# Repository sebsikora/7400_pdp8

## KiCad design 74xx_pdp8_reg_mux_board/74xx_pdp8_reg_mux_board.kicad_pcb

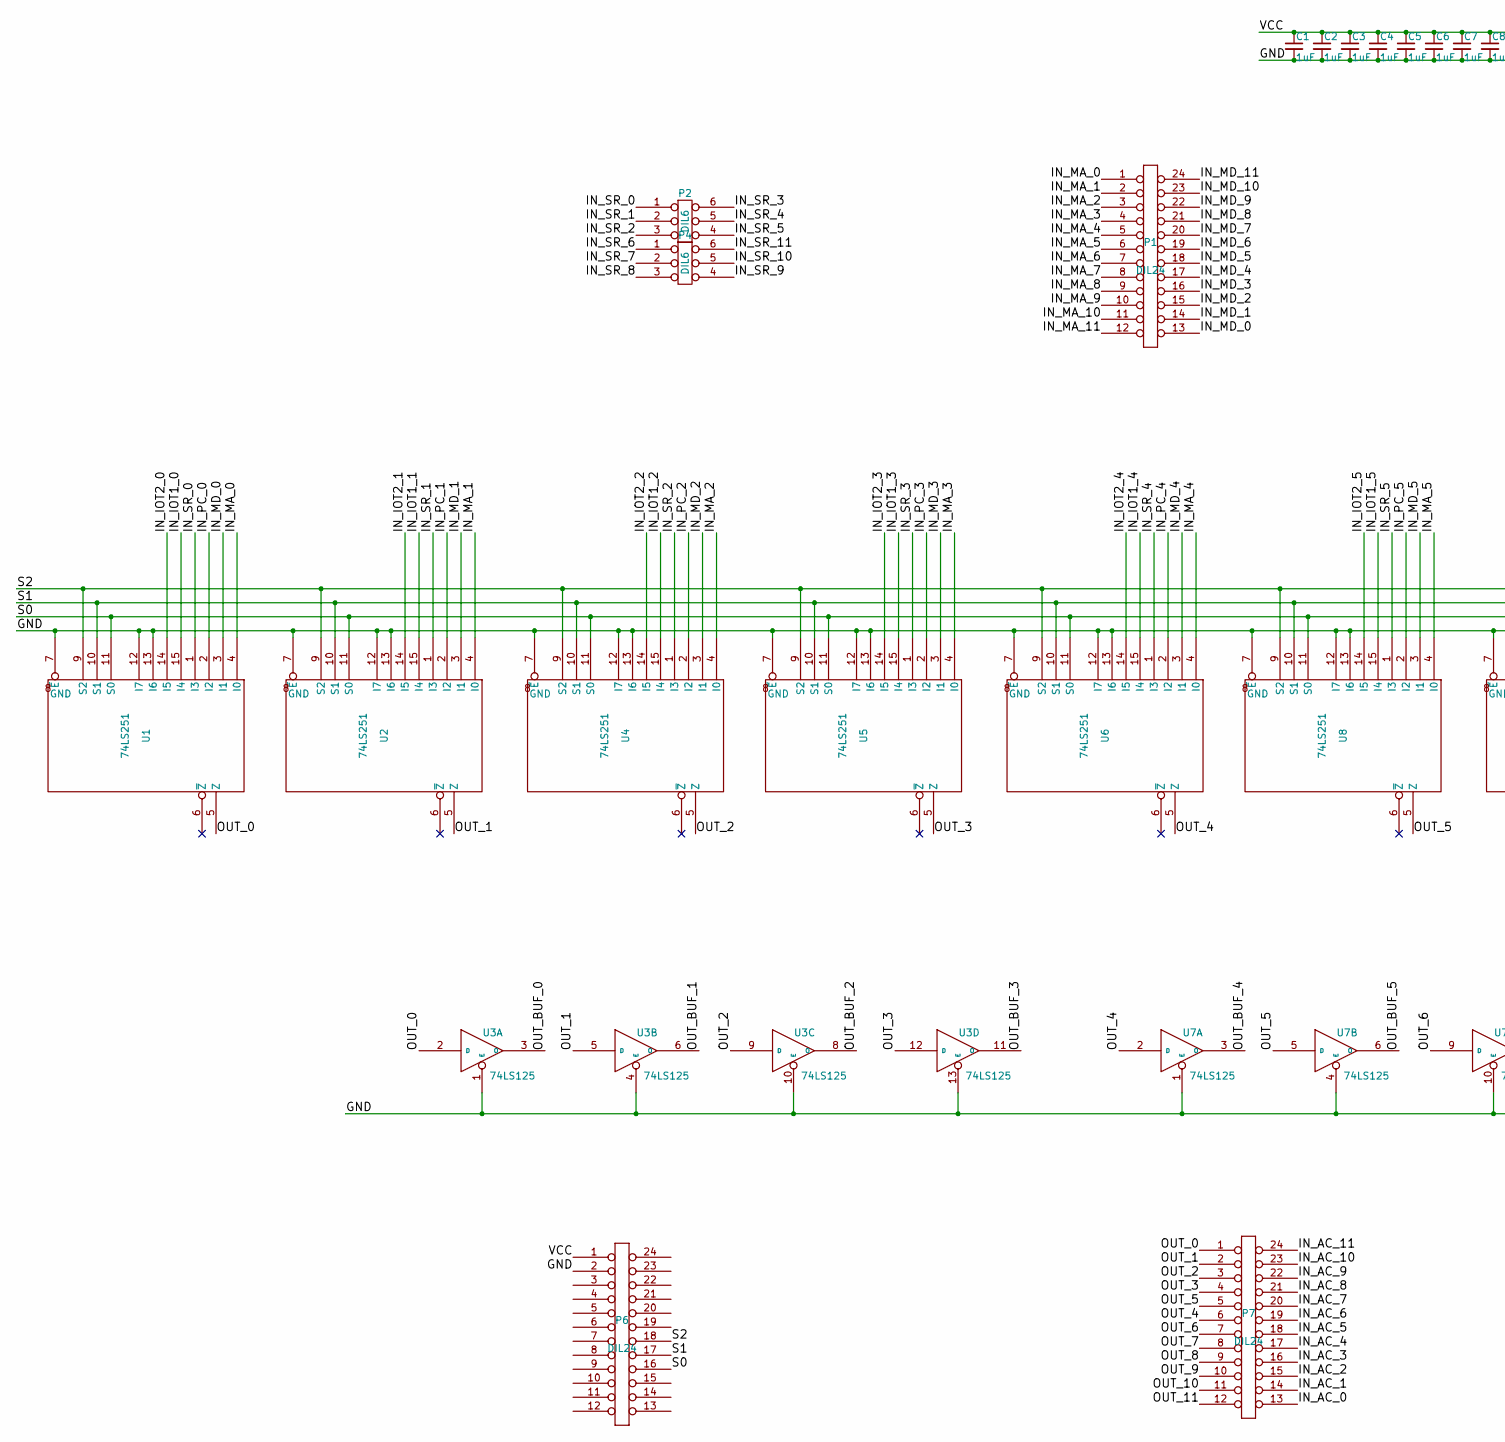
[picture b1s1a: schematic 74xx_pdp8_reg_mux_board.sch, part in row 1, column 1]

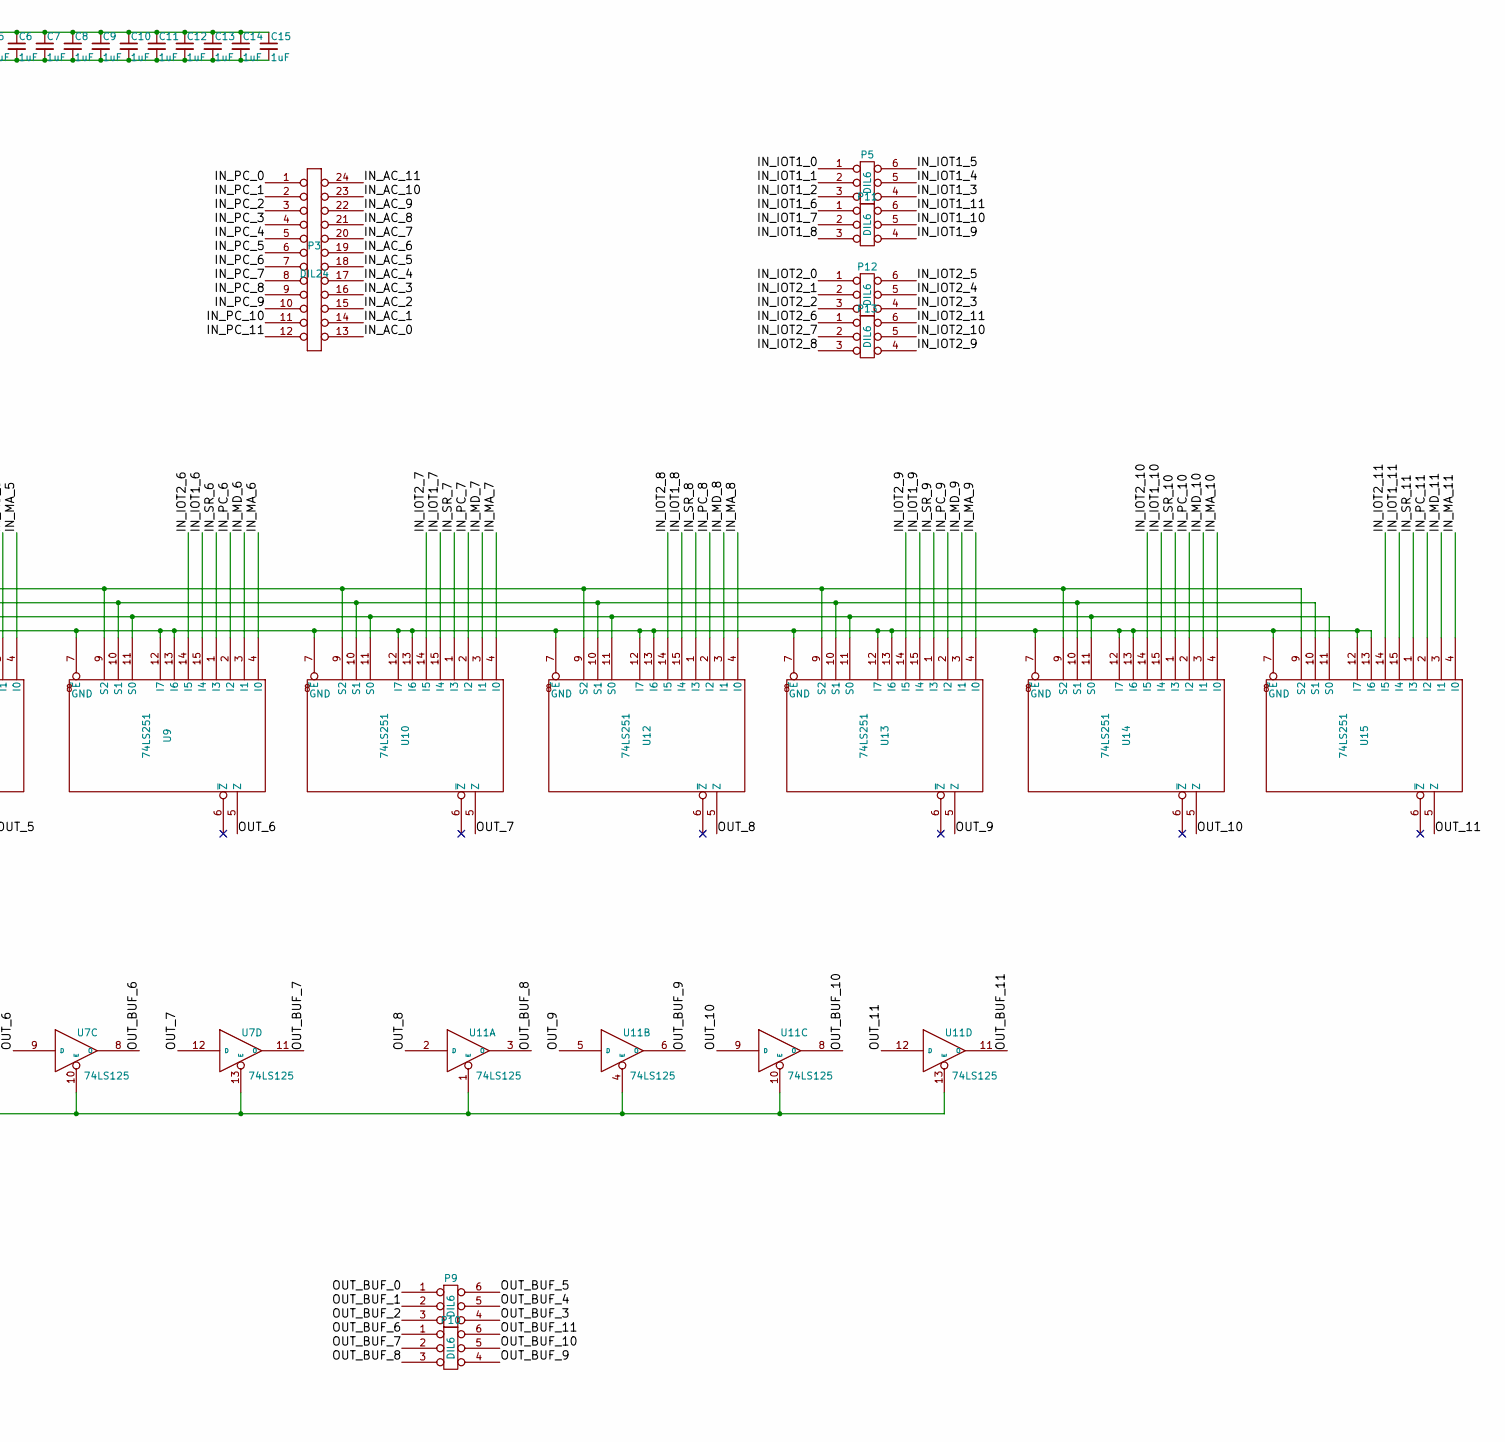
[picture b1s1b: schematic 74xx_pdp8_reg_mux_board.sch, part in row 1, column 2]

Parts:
C1, C2, C3, C4, C5, C6, C7, C8, C9, C10, C11, C12, C13, C14, C15: 1uF; C_Disc_D3_P2.5
P1, P3, P6, P7: DIL24; Socket_Strip_Straight_2x12
P2, P4, P5, P9, P10, P11, P12, P13: DIL6; Socket_Strip_Straight_2x03
U1, U2, U4, U5, U6, U8, U9, U10, U12, U13, U14, U15: 74LS251; DIP-16_W7.62mm
U3, U7, U11: 74LS125; DIP-14_W7.62mm

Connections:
/IN_AC_0: P3.13, P7.13
/IN_AC_1: P3.14, P7.14
/IN_AC_2: P3.15, P7.15
/IN_AC_3: P3.16, P7.16
/IN_AC_4: P3.17, P7.17
/IN_AC_5: P3.18, P7.18
/IN_AC_6: P3.19, P7.19
/IN_AC_7: P3.20, P7.20
/IN_AC_8: P3.21, P7.21
/IN_AC_9: P3.22, P7.22
/IN_AC_10: P3.23, P7.23
/IN_AC_11: P3.24, P7.24
/IN_IOT1_0: P5.1, U1.15 (I4)
/IN_IOT1_1: P5.2, U2.15 (I4)
/IN_IOT1_2: P5.3, U4.15 (I4)
/IN_IOT1_3: P5.4, U5.15 (I4)
/IN_IOT1_4: P5.5, U6.15 (I4)
/IN_IOT1_5: P5.6, U8.15 (I4)
/IN_IOT1_6: P11.1, U9.15 (I4)
/IN_IOT1_7: P11.2, U10.15 (I4)
/IN_IOT1_8: P11.3, U12.15 (I4)
/IN_IOT1_9: P11.4, U13.15 (I4)
/IN_IOT1_10: P11.5, U14.15 (I4)
/IN_IOT1_11: P11.6, U15.15 (I4)
/IN_IOT2_0: P12.1, U1.14 (I5)
/IN_IOT2_1: P12.2, U2.14 (I5)
/IN_IOT2_2: P12.3, U4.14 (I5)
/IN_IOT2_3: P12.4, U5.14 (I5)
/IN_IOT2_4: P12.5, U6.14 (I5)
/IN_IOT2_5: P12.6, U8.14 (I5)
/IN_IOT2_6: P13.1, U9.14 (I5)
/IN_IOT2_7: P13.2, U10.14 (I5)
/IN_IOT2_8: P13.3, U12.14 (I5)
/IN_IOT2_9: P13.4, U13.14 (I5)
/IN_IOT2_10: P13.5, U14.14 (I5)
/IN_IOT2_11: P13.6, U15.14 (I5)
/IN_MA_0: P1.1, U1.4 (I0)
/IN_MA_1: P1.2, U2.4 (I0)
/IN_MA_2: P1.3, U4.4 (I0)
/IN_MA_3: P1.4, U5.4 (I0)
/IN_MA_4: P1.5, U6.4 (I0)
/IN_MA_5: P1.6, U8.4 (I0)
/IN_MA_6: P1.7, U9.4 (I0)
/IN_MA_7: P1.8, U10.4 (I0)
/IN_MA_8: P1.9, U12.4 (I0)
/IN_MA_9: P1.10, U13.4 (I0)
/IN_MA_10: P1.11, U14.4 (I0)
/IN_MA_11: P1.12, U15.4 (I0)
/IN_MD_0: P1.13, U1.3 (I1)
/IN_MD_1: P1.14, U2.3 (I1)
/IN_MD_2: P1.15, U4.3 (I1)
/IN_MD_3: P1.16, U5.3 (I1)
/IN_MD_4: P1.17, U6.3 (I1)
/IN_MD_5: P1.18, U8.3 (I1)
/IN_MD_6: P1.19, U9.3 (I1)
/IN_MD_7: P1.20, U10.3 (I1)
/IN_MD_8: P1.21, U12.3 (I1)
/IN_MD_9: P1.22, U13.3 (I1)
/IN_MD_10: P1.23, U14.3 (I1)
/IN_MD_11: P1.24, U15.3 (I1)
/IN_PC_0: P3.1, U1.2 (I2)
/IN_PC_1: P3.2, U2.2 (I2)
/IN_PC_2: P3.3, U4.2 (I2)
/IN_PC_3: P3.4, U5.2 (I2)
/IN_PC_4: P3.5, U6.2 (I2)
/IN_PC_5: P3.6, U8.2 (I2)
/IN_PC_6: P3.7, U9.2 (I2)
/IN_PC_7: P3.8, U10.2 (I2)
/IN_PC_8: P3.9, U12.2 (I2)
/IN_PC_9: P3.10, U13.2 (I2)
/IN_PC_10: P3.11, U14.2 (I2)
/IN_PC_11: P3.12, U15.2 (I2)
/IN_SR_0: P2.1, U1.1 (I3)
/IN_SR_1: P2.2, U2.1 (I3)
/IN_SR_2: P2.3, U4.1 (I3)
/IN_SR_3: P2.6, U5.1 (I3)
/IN_SR_4: P2.5, U6.1 (I3)
/IN_SR_5: P2.4, U8.1 (I3)
/IN_SR_6: P4.1, U9.1 (I3)
/IN_SR_7: P4.2, U10.1 (I3)
/IN_SR_8: P4.3, U12.1 (I3)
/IN_SR_9: P4.4, U13.1 (I3)
/IN_SR_10: P4.5, U14.1 (I3)
/IN_SR_11: P4.6, U15.1 (I3)
/OUT_0: P7.1, U1.5 (Z), U3.2 (D)
/OUT_1: P7.2, U2.5 (Z), U3.5 (D)
/OUT_2: P7.3, U3.9 (D), U4.5 (Z)
/OUT_3: P7.4, U3.12 (D), U5.5 (Z)
/OUT_4: P7.6, U6.5 (Z), U7.2 (D)
/OUT_5: P7.5, U7.5 (D), U8.5 (Z)
/OUT_6: P7.7, U7.9 (D), U9.5 (Z)
/OUT_7: P7.8, U7.12 (D), U10.5 (Z)
/OUT_8: P7.9, U11.2 (D), U12.5 (Z)
/OUT_9: P7.10, U11.5 (D), U13.5 (Z)
/OUT_10: P7.11, U11.9 (D), U14.5 (Z)
/OUT_11: P7.12, U11.12 (D), U15.5 (Z)
/OUT_BUF_0: P9.1, U3.3 (O)
/OUT_BUF_1: P9.2, U3.6 (O)
/OUT_BUF_2: P9.3, U3.8 (O)
/OUT_BUF_3: P9.4, U3.11 (O)
/OUT_BUF_4: P9.5, U7.3 (O)
/OUT_BUF_5: P9.6, U7.6 (O)
/OUT_BUF_6: P10.1, U7.8 (O)
/OUT_BUF_7: P10.2, U7.11 (O)
/OUT_BUF_8: P10.3, U11.3 (O)
/OUT_BUF_9: P10.4, U11.6 (O)
/OUT_BUF_10: P10.5, U11.8 (O)
/OUT_BUF_11: P10.6, U11.11 (O)
/S0: P6.16, U1.11 (S0), U2.11 (S0), U4.11 (S0), U5.11 (S0), U6.11 (S0), U8.11 (S0), U9.11 (S0), U10.11 (S0), U12.11 (S0), U13.11 (S0), U14.11 (S0), U15.11 (S0)
/S1: P6.17, U1.10 (S1), U2.10 (S1), U4.10 (S1), U5.10 (S1), U6.10 (S1), U8.10 (S1), U9.10 (S1), U10.10 (S1), U12.10 (S1), U13.10 (S1), U14.10 (S1), U15.10 (S1)
/S2: P6.18, U1.9 (S2), U2.9 (S2), U4.9 (S2), U5.9 (S2), U6.9 (S2), U8.9 (S2), U9.9 (S2), U10.9 (S2), U12.9 (S2), U13.9 (S2), U14.9 (S2), U15.9 (S2)
GND: C1.2, C2.2, C3.2, C4.2, C5.2, C6.2, C7.2, C8.2, C9.2, C10.2, C11.2, C12.2, C13.2, C14.2, C15.2, P6.2, U1.7 (~E), U1.12 (I7), U1.13 (I6), U2.7 (~E), U2.12 (I7), U2.13 (I6), U3.1 (E), U3.4 (E), U3.7 (GND), U3.10 (E), U3.13 (E), U4.7 (~E), U4.12 (I7), U4.13 (I6), U5.7 (~E), U5.12 (I7), U5.13 (I6), U6.7 (~E), U6.12 (I7), U6.13 (I6), U7.1 (E), U7.4 (E), U7.7 (GND), U7.10 (E), U7.13 (E), U8.7 (~E), U8.12 (I7), U8.13 (I6), U9.7 (~E), U9.12 (I7), U9.13 (I6), U10.7 (~E), U10.12 (I7), U10.13 (I6), U11.1 (E), U11.4 (E), U11.7 (GND), U11.10 (E), U11.13 (E), U12.7 (~E), U12.12 (I7), U12.13 (I6), U13.7 (~E), U13.12 (I7), U13.13 (I6), U14.7 (~E), U14.12 (I7), U14.13 (I6), U15.7 (~E), U15.12 (I7), U15.13 (I6)
VCC: C1.1, C2.1, C3.1, C4.1, C5.1, C6.1, C7.1, C8.1, C9.1, C10.1, C11.1, C12.1, C13.1, C14.1, C15.1, P6.1, U1.16 (VCC), U2.16 (VCC), U3.14 (VCC), U4.16 (VCC), U5.16 (VCC), U6.16 (VCC), U7.14 (VCC), U8.16 (VCC), U9.16 (VCC), U10.16 (VCC), U11.14 (VCC), U12.16 (VCC), U13.16 (VCC), U14.16 (VCC), U15.16 (VCC)

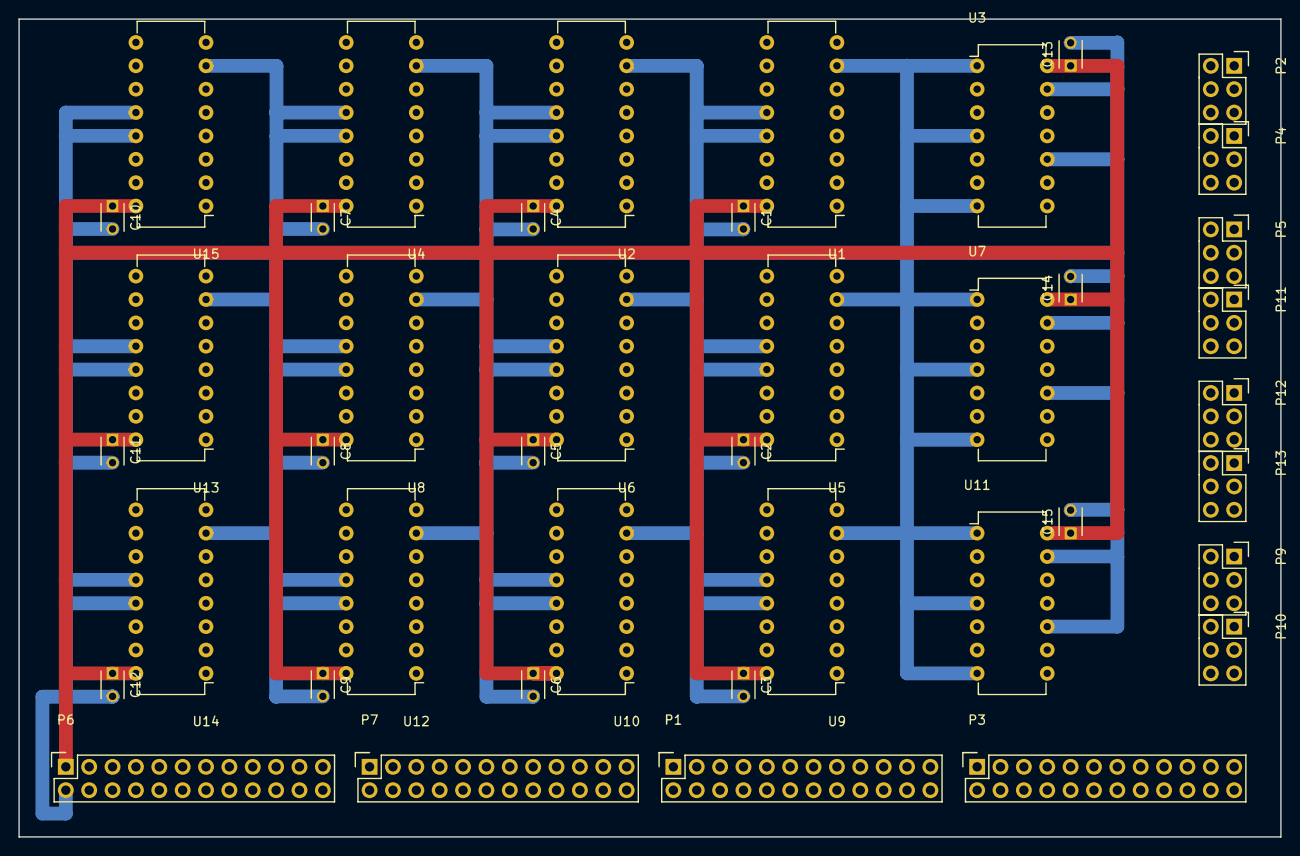
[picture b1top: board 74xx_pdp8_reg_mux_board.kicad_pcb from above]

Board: 4 copper layers, 137.2 x 88.9 mm, 42 parts (0 on the bottom side), 113 nets.

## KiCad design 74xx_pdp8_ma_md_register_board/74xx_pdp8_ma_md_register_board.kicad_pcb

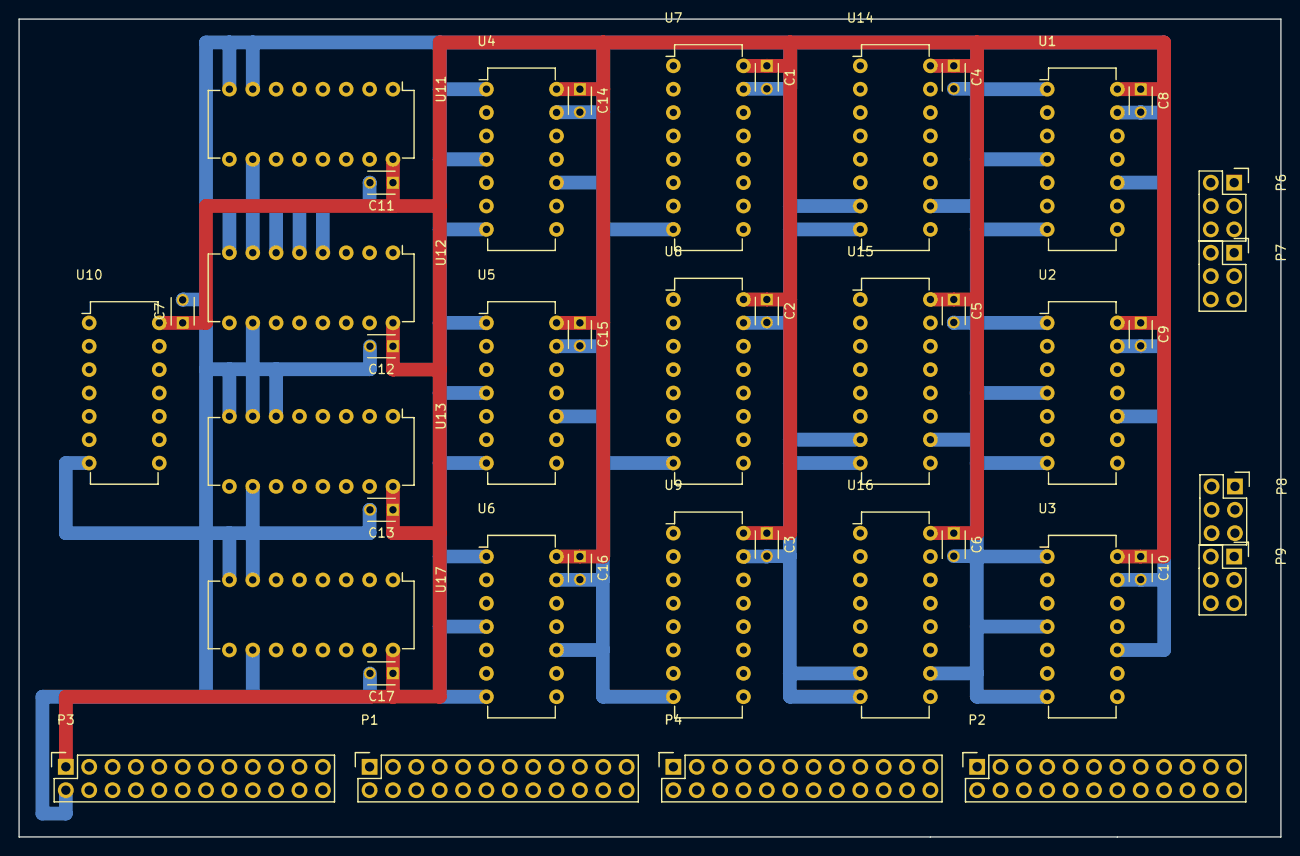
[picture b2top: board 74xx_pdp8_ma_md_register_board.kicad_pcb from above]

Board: 4 copper layers, 137.2 x 88.9 mm, 42 parts (0 on the bottom side), 100 nets.

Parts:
C1, C2, C3, C4, C5, C6, C7, C8, C9, C10, C11, C12, C13, C14, C15, C16, C17: 1uF; C_Disc_D3_P2.5
P1, P2, P3, P4: DIL24; Socket_Strip_Straight_2x12
P6, P7, P8, P9: DIL6; Socket_Strip_Straight_2x03
U1, U2, U3, U4, U5, U6: 74HC125; DIP-14_W7.62mm
U7, U8, U9: 74HC257; DIP-16_W7.62mm
U10: 74HC04; DIP-14_W7.62mm
U11, U12, U13, U14, U15, U16, U17: 74HC163; DIP-16_W7.62mm

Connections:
/CLEAR_HI_MA: P3.5, U10.3
/CLEAR_LO_MA: P3.7, U10.9
/CLEAR_MD: P3.9, U10.13
/CLK: P3.3, U11.2, U12.2, U13.2, U14.2, U15.2, U16.2, U17.2
/INSEL: U7.1, U8.1, U9.1
/IN_ALU_0: P1.1, U7.10, U11.3
/IN_ALU_1: P1.2, U7.13, U11.4
/IN_ALU_2: P1.3, U7.6, U11.5
/IN_ALU_3: P1.4, U7.3, U11.6
/IN_ALU_4: P1.5, U8.10, U12.3
/IN_ALU_5: P1.6, U8.13, U13.3
/IN_ALU_6: P1.7, U8.6, U13.4
/IN_ALU_7: P1.8, U8.3, U13.5
/IN_ALU_8: P1.9, U9.10, U17.3
/IN_ALU_9: P1.10, U9.13, U17.4
/IN_ALU_10: P1.11, U9.6, U17.5
/IN_ALU_11: P1.12, U9.3, U17.6
/IN_MEM_0: P1.13, U7.11
/IN_MEM_1: P1.14, U7.14
/IN_MEM_2: P1.15, U7.5
/IN_MEM_3: P1.16, U7.2
/IN_MEM_4: P1.17, U8.11
/IN_MEM_5: P1.18, U8.14
/IN_MEM_6: P1.19, U8.5
/IN_MEM_7: P1.20, U8.2
/IN_MEM_8: P1.21, U9.11
/IN_MEM_9: P1.22, U9.14
/IN_MEM_10: P1.23, U9.5
/IN_MEM_11: P1.24, U9.2
/IN_SEL_0: U7.9, U14.3
/IN_SEL_1: U7.12, U14.4
/IN_SEL_2: U7.7, U14.5
/IN_SEL_3: U7.4, U14.6
/IN_SEL_4: U8.9, U15.3
/IN_SEL_5: U8.12, U15.4
/IN_SEL_6: U8.7, U15.5
/IN_SEL_7: U8.4, U15.6
/IN_SEL_8: U9.9, U16.3
/IN_SEL_9: U9.12, U16.4
/IN_SEL_10: U9.7, U16.5
/IN_SEL_11: U9.4, U16.6
/LOAD_HI_MA: P3.4, U10.1
/LOAD_LO_MA: P3.6, U10.5
/LOAD_MD: P3.8, U10.11
/OUT_BUF_MA_0: P6.1, U1.3
/OUT_BUF_MA_1: P6.2, U1.6
/OUT_BUF_MA_2: P6.3, U1.8
/OUT_BUF_MA_3: P7.1, U1.11
/OUT_BUF_MA_4: P7.2, U2.3
/OUT_BUF_MA_5: P7.3, U2.6
/OUT_BUF_MA_6: P7.4, U2.8
/OUT_BUF_MA_7: P7.5, U2.11
/OUT_BUF_MA_8: P7.6, U3.3
/OUT_BUF_MA_9: P6.4, U3.6
/OUT_BUF_MA_10: P6.5, U3.8
/OUT_BUF_MA_11: P6.6, U3.11
/OUT_BUF_MD_0: P8.1, U4.3
/OUT_BUF_MD_1: P8.2, U4.6
/OUT_BUF_MD_2: P8.3, U4.8
/OUT_BUF_MD_3: P9.1, U4.11
/OUT_BUF_MD_4: P9.2, U5.3
/OUT_BUF_MD_5: P9.3, U5.6
/OUT_BUF_MD_6: P9.4, U5.8
/OUT_BUF_MD_7: P9.5, U5.11
/OUT_BUF_MD_8: P9.6, U6.3
/OUT_BUF_MD_9: P8.4, U6.6
/OUT_BUF_MD_10: P8.5, U6.8
/OUT_BUF_MD_11: P8.6, U6.11
/OUT_MA_0: P4.1, U1.2, U11.14
/OUT_MA_1: P4.2, U1.5, U11.13
/OUT_MA_2: P4.3, U1.9, U11.12
/OUT_MA_3: P4.4, U1.12, U11.11
/OUT_MA_4: P4.5, U2.2, U12.14
/OUT_MA_5: P4.6, U2.5, U13.14
/OUT_MA_6: P4.7, U2.9, U13.13
/OUT_MA_7: P4.8, U2.12, U13.12
/OUT_MA_8: P4.9, U3.2, U17.14
/OUT_MA_9: P4.10, U3.5, U17.13
/OUT_MA_10: P4.11, U3.9, U17.12
/OUT_MA_11: P4.12, U3.12, U17.11
/OUT_MD_0: P4.13, U4.2, U14.14
/OUT_MD_1: P4.14, U4.5, U14.13
/OUT_MD_2: P4.15, U4.9, U14.12
/OUT_MD_3: P4.16, U4.12, U14.11
/OUT_MD_4: P4.17, U5.2, U15.14
/OUT_MD_5: P4.18, U5.5, U15.13
/OUT_MD_6: P4.19, U5.9, U15.12
/OUT_MD_7: P4.20, U5.12, U15.11
/OUT_MD_8: P4.21, U6.2, U16.14
/OUT_MD_9: P4.22, U6.5, U16.13
/OUT_MD_10: P4.23, U6.9, U16.12
/OUT_MD_11: P4.24, U6.12, U16.11
GND: C1.2, C2.2, C3.2, C4.2, C5.2, C6.2, C7.2, C8.2, C9.2, C10.2, C11.2, C12.2, C13.2, C14.2, C15.2, C16.2, C17.2, P3.2, U1.1, U1.4, U1.7, U1.10, U1.13, U2.1, U2.4, U2.7, U2.10, U2.13, U3.1, U3.4, U3.7, U3.10, U3.13, U4.1, U4.4, U4.7, U4.10, U4.13, U5.1, U5.4, U5.7, U5.10, U5.13, U6.1, U6.4, U6.7, U6.10, U6.13, U7.8, U7.15, U8.8, U8.15, U9.8, U9.15, U10.7, U11.7, U11.8, U11.10, U12.4, U12.5, U12.6, U12.7, U12.8, U12.10, U13.6, U13.7, U13.8, U13.10, U14.7, U14.8, U14.10, U15.7, U15.8, U15.10, U16.7, U16.8, U16.10, U17.7, U17.8, U17.10
unnamed: U10.2, U11.9, U12.9
unnamed: U10.4, U11.1, U12.1
unnamed: U10.6, U13.9, U17.9
unnamed: U10.8, U13.1, U17.1
unnamed: U10.10, U14.9, U15.9, U16.9
unnamed: U10.12, U14.1, U15.1, U16.1
VCC: C1.1, C2.1, C3.1, C4.1, C5.1, C6.1, C7.1, C8.1, C9.1, C10.1, C11.1, C12.1, C13.1, C14.1, C15.1, C16.1, C17.1, P3.1, U1.14, U2.14, U3.14, U4.14, U5.14, U6.14, U7.16, U8.16, U9.16, U10.14, U11.16, U12.16, U13.16, U14.16, U15.16, U16.16, U17.16

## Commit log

2018-04-04 First commit.
2018-04-04 Revised and tidied register mux schematic and 'pcb' layout.
2018-04-05 Roughed-out layout of register multiplexor board. Need to double check dimensions of twin register board.
2018-04-07 Lots of tidying up. Rationalised connectors at register board 'output' end. Connectors matched on register and mux boards.
2018-04-07 Big changes - elected to switch to board interconnections along one long edge only. Boards to connect to backplane via right-angled DIL connectors. Both register boards and register mux boards thusly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
